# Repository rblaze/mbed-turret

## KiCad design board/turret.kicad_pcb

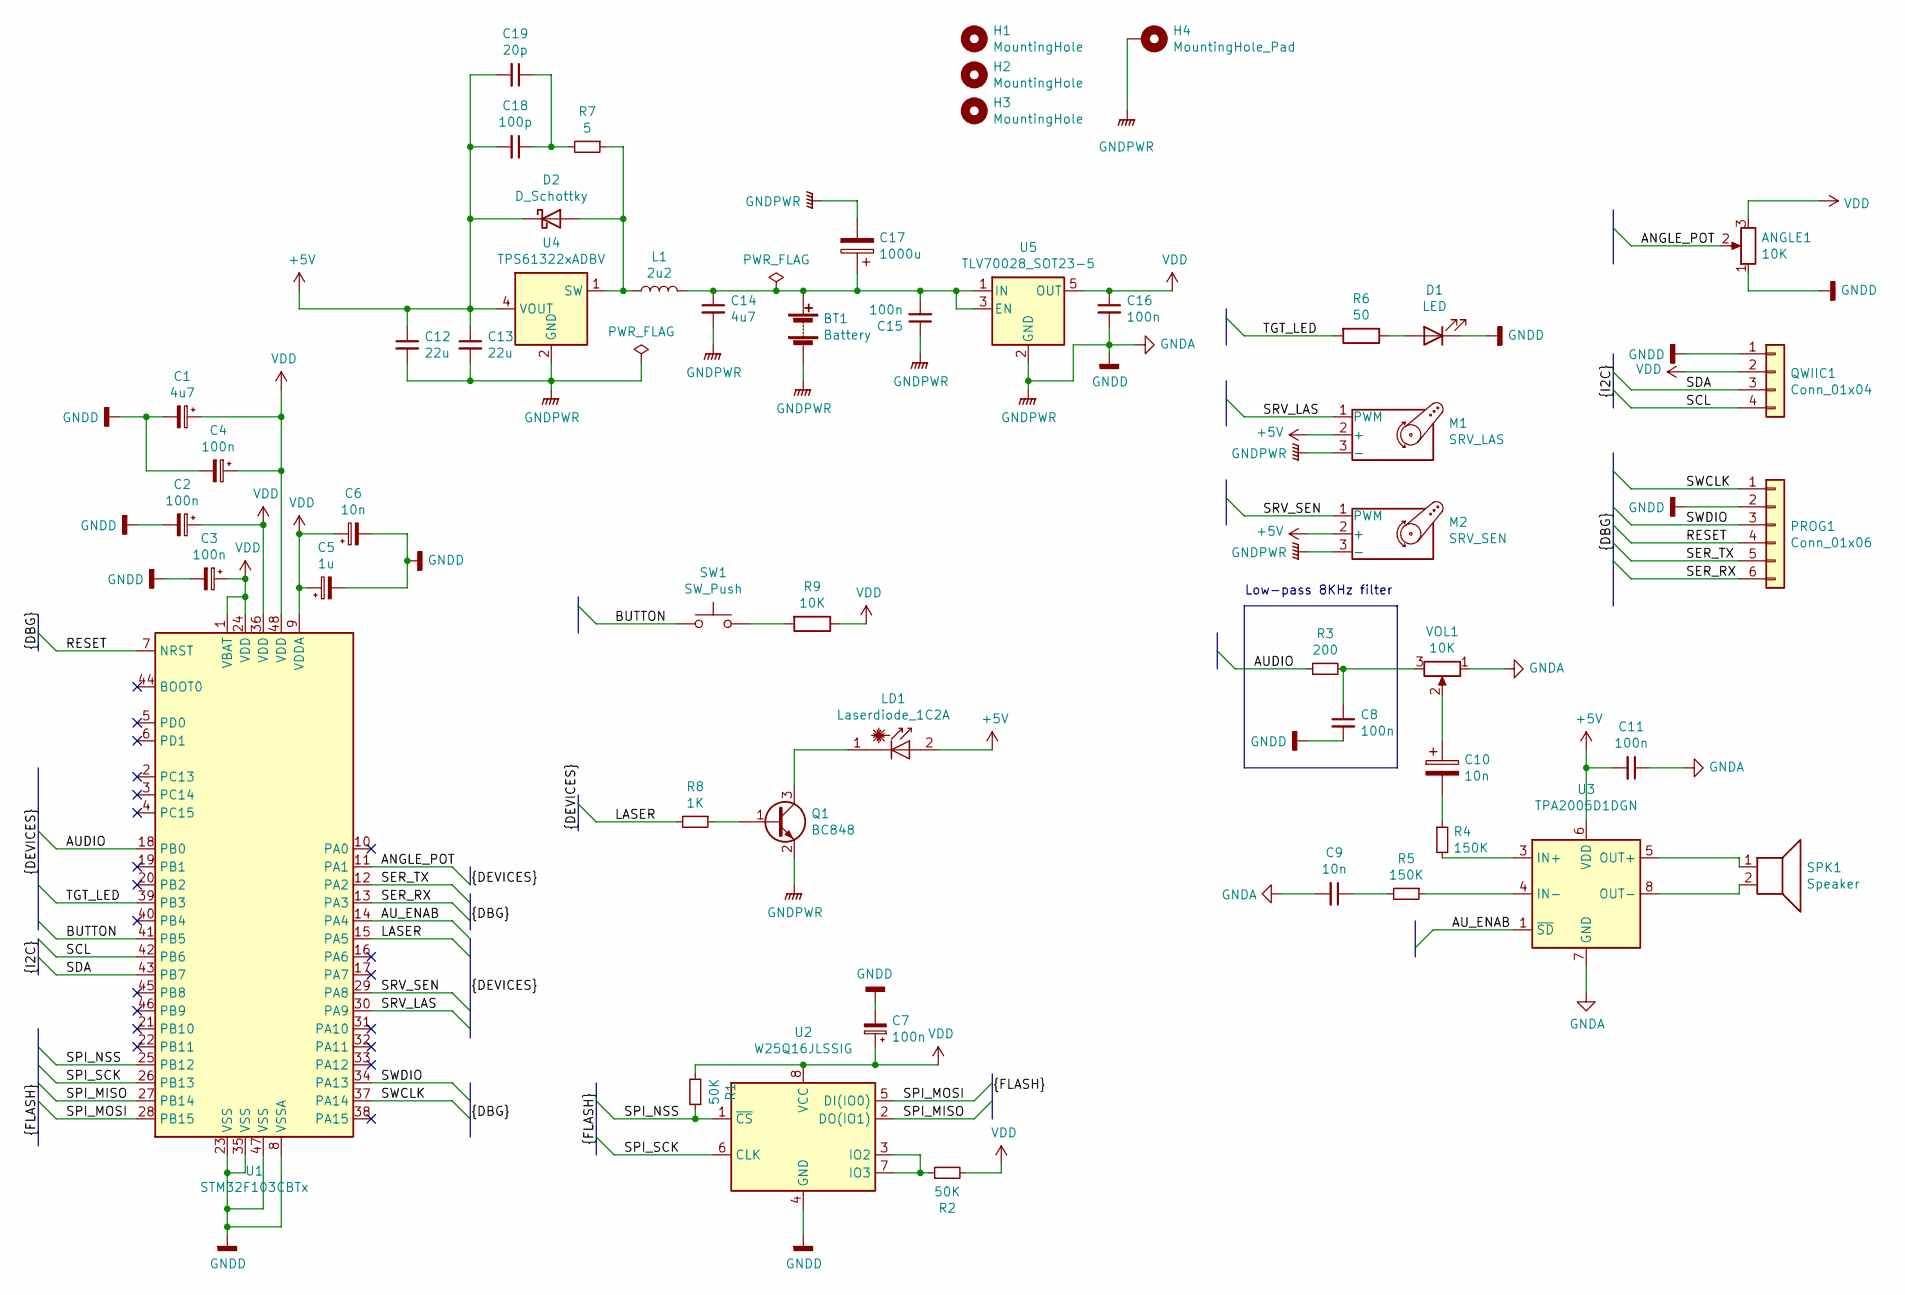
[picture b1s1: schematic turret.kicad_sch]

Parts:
ANGLE1: 10K; Molex_KK-254_AE-6410-03A_1x03_P2.54mm_Vertical
BT1: Battery; Molex_KK-254_AE-6410-02A_1x02_P2.54mm_Vertical
C1, C14: 4u7; C_0402_1005Metric
C2, C3, C4, C7, C8, C11, C15, C16: 100n; C_0402_1005Metric
C5: 1u; C_0402_1005Metric
C6, C9, C10: 10n; C_0402_1005Metric
C12, C13: 22u; C_0603_1608Metric
C17: 1000u; CP_Radial_D10.0mm_P5.00mm
C18: 100p; C_0402_1005Metric
C19: 20p; C_0402_1005Metric
D1: LED; LED_0805_2012Metric
D2: D_Schottky; D_SOD-323
H1, H2, H3: MountingHole; JLCPCB_Tooling_Hole
H4: MountingHole_Pad; MountingHole_2.2mm_M2_DIN965_Pad
L1: 2u2; L_1008_2520Metric
LD1: Laserdiode_1C2A; Molex_KK-254_AE-6410-02A_1x02_P2.54mm_Vertical
M1: SRV_LAS; Molex_KK-254_AE-6410-03A_1x03_P2.54mm_Vertical
M2: SRV_SEN; Molex_KK-254_AE-6410-03A_1x03_P2.54mm_Vertical
PROG1: Conn_01x06; Molex_SPOX_5267-06A_1x06_P2.50mm_Vertical
Q1: BC848; SOT-23
QWIIC1: Conn_01x04; JST_SH_BM04B-SRSS-TB_1x04-1MP_P1.00mm_Vertical
R1, R2: 50K; R_0402_1005Metric
R3: 200; R_0402_1005Metric
R4, R5: 150K; R_0402_1005Metric
R6: 50; R_0402_1005Metric
R7: 5; R_0402_1005Metric
R8: 1K; R_0402_1005Metric
R9: 10K; R_0402_1005Metric
SPK1: Speaker; Molex_KK-254_AE-6410-02A_1x02_P2.54mm_Vertical
SW1: SW_Push; SW_SPST_PTS810
U1: STM32F103CBTx; LQFP-48_7x7mm_P0.5mm
U2: W25Q16JLSSIG; SOIC-8_5.23x5.23mm_P1.27mm
U3: TPA2005D1DGN; TI_VSSOP-PowerPAD-8_3.0x3.0mm_P0.65mm_ThermalVias
U4: TPS61322xADBV; SOT-23-5
U5: TLV70028_SOT23-5; SOT-23-5
VOL1: 10K; Molex_KK-254_AE-6410-03A_1x03_P2.54mm_Vertical

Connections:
+5V: C11.2, C12.1, C13.1, C18.2, C19.2, D2.1 (K), LD1.2 (A), M1.2 (+), M2.2 (+), U3.6 (VDD), U4.3 (NC), U4.4 (VOUT)
/ANGLE_POT: ANGLE1.2, U1.11 (PA1)
/AUDIO: R3.1, U1.18 (PB0)
/AU_ENAB: U1.14 (PA4), U3.1 (~SD)
/BUTTON: SW1.1, U1.41 (PB5)
/LASER: R8.2, U1.15 (PA5)
/RESET: PROG1.4, U1.7 (NRST)
/SCL: QWIIC1.4, U1.42 (PB6)
/SDA: QWIIC1.3, U1.43 (PB7)
/SER_RX: PROG1.6, U1.13 (PA3)
/SER_TX: PROG1.5, U1.12 (PA2)
/SPI_MISO: U1.27 (PB14), U2.2 (DO(IO1))
/SPI_MOSI: U1.28 (PB15), U2.5 (DI(IO0))
/SPI_NSS: R1.1, U1.25 (PB12), U2.1 (~CS)
/SPI_SCK: U1.26 (PB13), U2.6 (CLK)
/SRV_LAS: M1.1 (PWM), U1.30 (PA9)
/SRV_SEN: M2.1 (PWM), U1.29 (PA8)
/SWCLK: PROG1.1, U1.37 (PA14)
/SWDIO: PROG1.3, U1.34 (PA13)
/TGT_LED: R6.2, U1.39 (PB3)
GNDA: ANGLE1.1, BT1.2 (-), C1.2, C2.2, C3.2, C4.2, C5.2, C6.2, C7.2, C8.2, C9.2, C11.1, C12.2, C13.2, C14.2, C15.1, C16.2, C17.2, D1.1 (K), H4.1, M1.3 (-), M2.3 (-), PROG1.2, Q1.2 (E), QWIIC1.1, U1.8 (VSSA), U1.23 (VSS), U1.35 (VSS), U1.47 (VSS), U2.4 (GND), U3.7 (GND), U3.9, U4.2 (GND), U4.5 (NC), U5.2 (GND), U5.4 (NC), VOL1.1
unnamed: BT1.1 (+), C14.1, C15.2, C17.1, L1.2, U5.1 (IN), U5.3 (EN)
unnamed: C8.1, R3.2, VOL1.3
unnamed: C9.1, R5.2
unnamed: C10.1, VOL1.2
unnamed: C10.2, R4.1
unnamed: C18.1, C19.1, R7.2
unnamed: D1.2 (A), R6.1
unnamed: D2.2 (A), L1.1, R7.1, U4.1 (SW)
unnamed: LD1.1 (K), Q1.3 (C)
unnamed: Q1.1 (B), R8.1
unnamed: R2.1, U2.3 (IO2), U2.7 (IO3)
unnamed: R4.2, U3.3 (IN+)
unnamed: R5.1, U3.4 (IN-)
unnamed: R9.2, SW1.2
unnamed: SPK1.1, U3.5 (OUT+)
unnamed: SPK1.2, U3.8 (OUT-)
VDD: ANGLE1.3, C1.1, C2.1, C3.1, C4.1, C5.1, C6.1, C7.1, C16.1, QWIIC1.2, R1.2, R2.2, R9.1, U1.1 (VBAT), U1.9 (VDDA), U1.24 (VDD), U1.36 (VDD), U1.48 (VDD), U2.8 (VCC), U5.5 (OUT)

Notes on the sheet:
Low-pass 8KHz filter

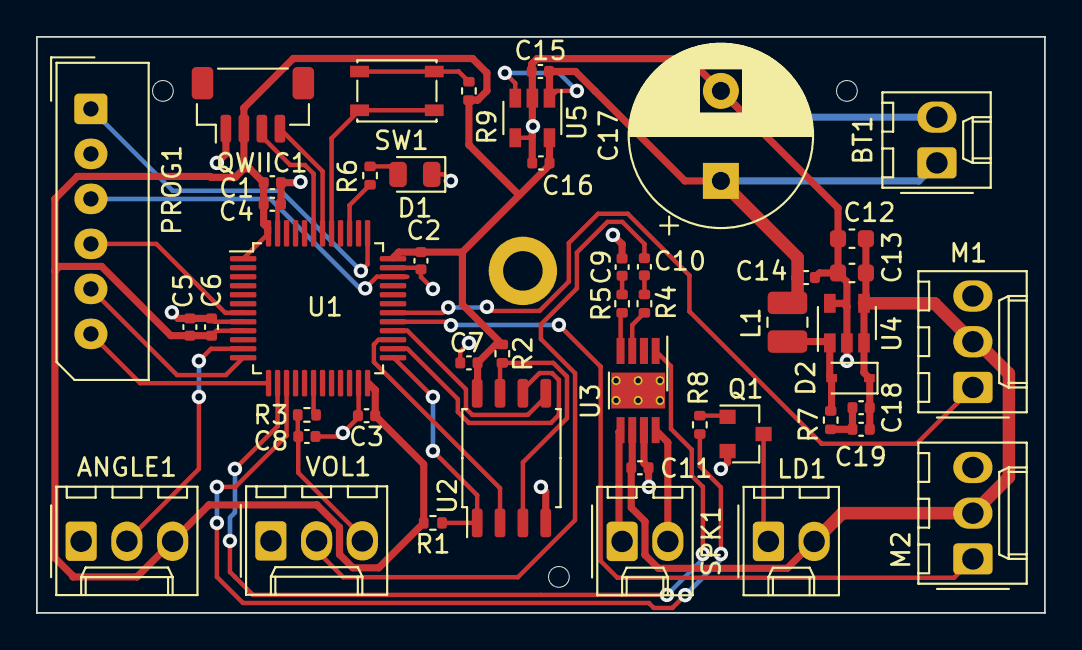
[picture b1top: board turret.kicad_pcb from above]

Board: 2 copper layers, 56.0 x 32.0 mm, 51 parts (0 on the bottom side), 38 nets.

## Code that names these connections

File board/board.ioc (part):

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Mcu.Name=STM32F103R(8-B)Tx
Mcu.Package=LQFP64
Mcu.UserName=STM32F103RBTx
PA1.GPIOParameters=GPIO_Label
PA1.GPIO_Label=PA1 [Angle setting]
PA1.Signal=ADCx_IN1
PA13.Mode=Serial_Wire
PA13.Signal=SYS_JTMS-SWDIO
PA14.Mode=Serial_Wire
PA14.Signal=SYS_JTCK-SWCLK
PA2.Mode=Asynchronous
PA2.Signal=USART2_TX
PA3.Mode=Asynchronous
PA3.Signal=USART2_RX
PA4.GPIOParameters=GPIO_Label
PA4.GPIO_Label=PA4 [Audio Disable]
PA4.Signal=GPIO_Output
PA5.GPIOParameters=GPIO_Label
PA5.GPIO_Label=PA5 [Laser]
PA5.Signal=GPIO_Output
PA8.GPIOParameters=GPIO_Label
PA8.GPIO_Label=PA8 [Servo PWM]
PA8.Signal=S_TIM1_CH1
PA9.GPIOParameters=GPIO_Label
PA9.GPIO_Label=PA9 [Laser PWM]
PA9.Signal=S_TIM1_CH2
PB0.GPIOParameters=GPIO_Label
PB0.GPIO_Label=PB0 [Audio]
PB0.Signal=S_TIM3_CH3
PB12.Mode=NSS_Signal_Hard_Output
PB12.Signal=SPI2_NSS
PB13.Mode=Full_Duplex_Master
PB13.Signal=SPI2_SCK
PB14.Mode=Full_Duplex_Master
PB14.Signal=SPI2_MISO
PB15.Mode=Full_Duplex_Master
PB15.Signal=SPI2_MOSI
PB3.GPIOParameters=GPIO_Label
PB3.GPIO_Label=PB3 [Contact]
PB3.Signal=GPIO_Output
PB5.GPIOParameters=GPIO_PuPd,GPIO_Label
PB5.GPIO_Label=PB5 [Button]
PB5.GPIO_PuPd=GPIO_PULLDOWN
PB5.Signal=GPIO_Input
PB6.Mode=I2C
PB6.Signal=I2C1_SCL
PB7.Mode=I2C
PB7.Signal=I2C1_SDA
board=custom

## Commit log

2019-11-16 Initial ranging pass
2019-11-17 One-way tracking and targeting
2019-11-17 Bidirectional scan
2019-11-25 Add audio effects
2019-11-25 Update libraries
2019-11-25 Add servo range adjustment
2019-11-25 Change callbacks to events
2019-11-25 Use events in AudioPlayer API
2019-12-13 Event-based code
2019-12-22 Classless Audio
2019-12-22 Use FSM for Audio
2019-12-24 Drop clock ticker
2019-12-24 Ranging calibration
2019-12-25 Add scan mode
2019-12-25 Add laser targeting
2019-12-28 Port to Maple Mini
2019-12-28 Reset PRNG using calibration time.
2019-12-29 Use calibration pot to init RNG.
2020-05-23 Rewrite FSM version
2020-06-09 Update sensor library
2020-06-09 Update board config
2020-06-14 Update audio port
2020-12-20 Add board design
2021-01-15 Add sound files
2021-01-18 Add MCU to board
2021-01-18 Add audio amplifier
2021-01-19 Add servos
2021-01-19 Add rest of parts except power
2021-01-20 Assign most components
2021-02-01 Relocate components to tested pins
2021-02-01 Switch to DMA-based audio player
2021-02-05 Fix pin assignment
2021-02-12 Add 5V boost
2021-02-12 Move LEDs to higher-powered pins
2021-02-12 Add 2V8 regulator
2021-02-13 Partially route board
2021-03-02 Route PCB
2021-03-02 Add PCB design
2021-03-05 Reroute 3v3 power
2021-03-06 Add mounting holes
2021-03-06 Update gitignore
2021-04-15 Partial routing
2021-04-16 Add tooling holes
2022-03-31 Update to kicad 6
2022-04-08 Board layout complete
2022-04-11 Fix silkscreen overlaps
2022-04-12 Adjust component clearances for assembly
2022-04-12 Update plot settings
2022-07-22 Update to mbed-os 6.15.1 and mbed CLI 2
2022-07-26 Add VSCode files, clang-format config and reformat sources
2022-10-15 Add CubeMX project
